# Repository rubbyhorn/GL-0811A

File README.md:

# GL-0811A
Dimmer reverse engineering

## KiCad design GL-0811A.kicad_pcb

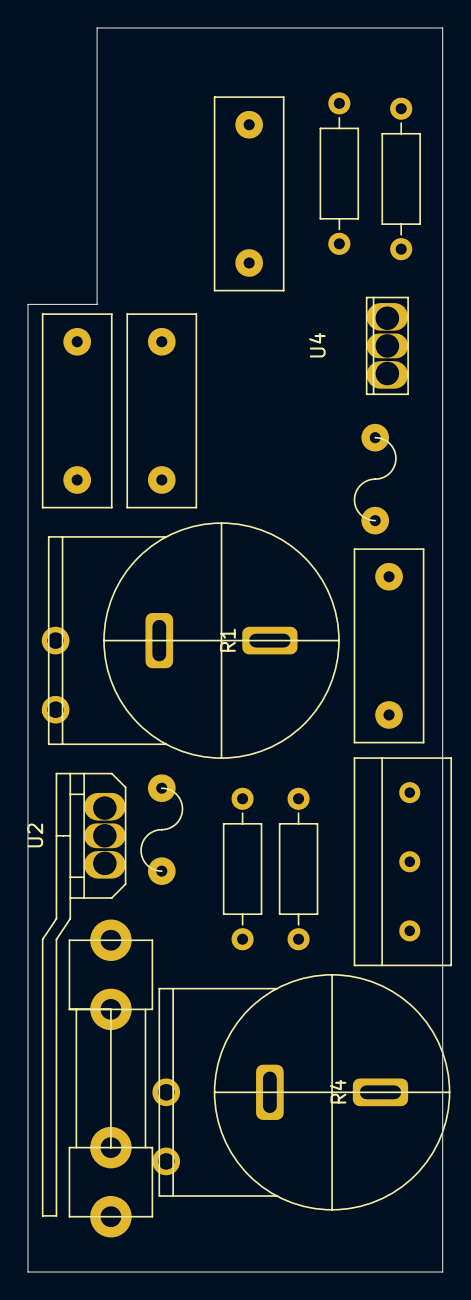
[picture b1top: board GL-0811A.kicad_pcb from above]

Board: 2 copper layers, 30.0 x 90.0 mm, 16 parts (0 on the bottom side), 11 nets, no tracks yet.

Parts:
C1, C2, C3, C4: C; C1
FU1: F1; Fuse
FU2, FU3: F1; Fuse2
R1, R4: R+SW
R2, R3, R5, R6: R; R_Axial_DIN0207_L6.3mm_D2.5mm_P10.16mm_Horizontal
U2: Semistor; sem1
U4: Semistor; sem2
X4: CONN_3; CON1

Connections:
unnamed: C1.1, C3.1, FU1.2, FU2.1, FU3.1, R1.3, R4.3
unnamed: C1.2, C2.2, U2.2
unnamed: C2.1, R1.2
unnamed: C3.2, C4.2, U4.2
unnamed: C4.1, R4.2
unnamed: R1.1, R2.2
unnamed: R1.4, R2.1
unnamed: R3.2, U2.3
unnamed: R4.1, R5.2
unnamed: R4.4, R5.1
unnamed: R6.2, U4.3

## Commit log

2021-03-26 Init
2021-03-26 26.03
2021-03-27 28.03
2021-03-28 28.03/2
